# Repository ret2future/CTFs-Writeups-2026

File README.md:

# CTFs 2026 Organized

This folder groups 2026 CTF challenges by event.

- Structure uses symlinks to original challenge folders (no duplicate copies).
- Each challenge appears under one CTF event in this organized view.
- Source folders remain unchanged.

Events included:

- UMassCTF_2026
- Index_2026_TAMUctf
- DawgCTF_2026
- Midnight_Flag_CTF_EXECUTION_2026
- PsychCTF_2026
- UTCTF_2026
- BlueHens_CTF_2026
- RedFox_CTF_2026
- Ramadan_CTF_2026
- Incognito_7_0_2026
- Squ1rrel_CTF_2026

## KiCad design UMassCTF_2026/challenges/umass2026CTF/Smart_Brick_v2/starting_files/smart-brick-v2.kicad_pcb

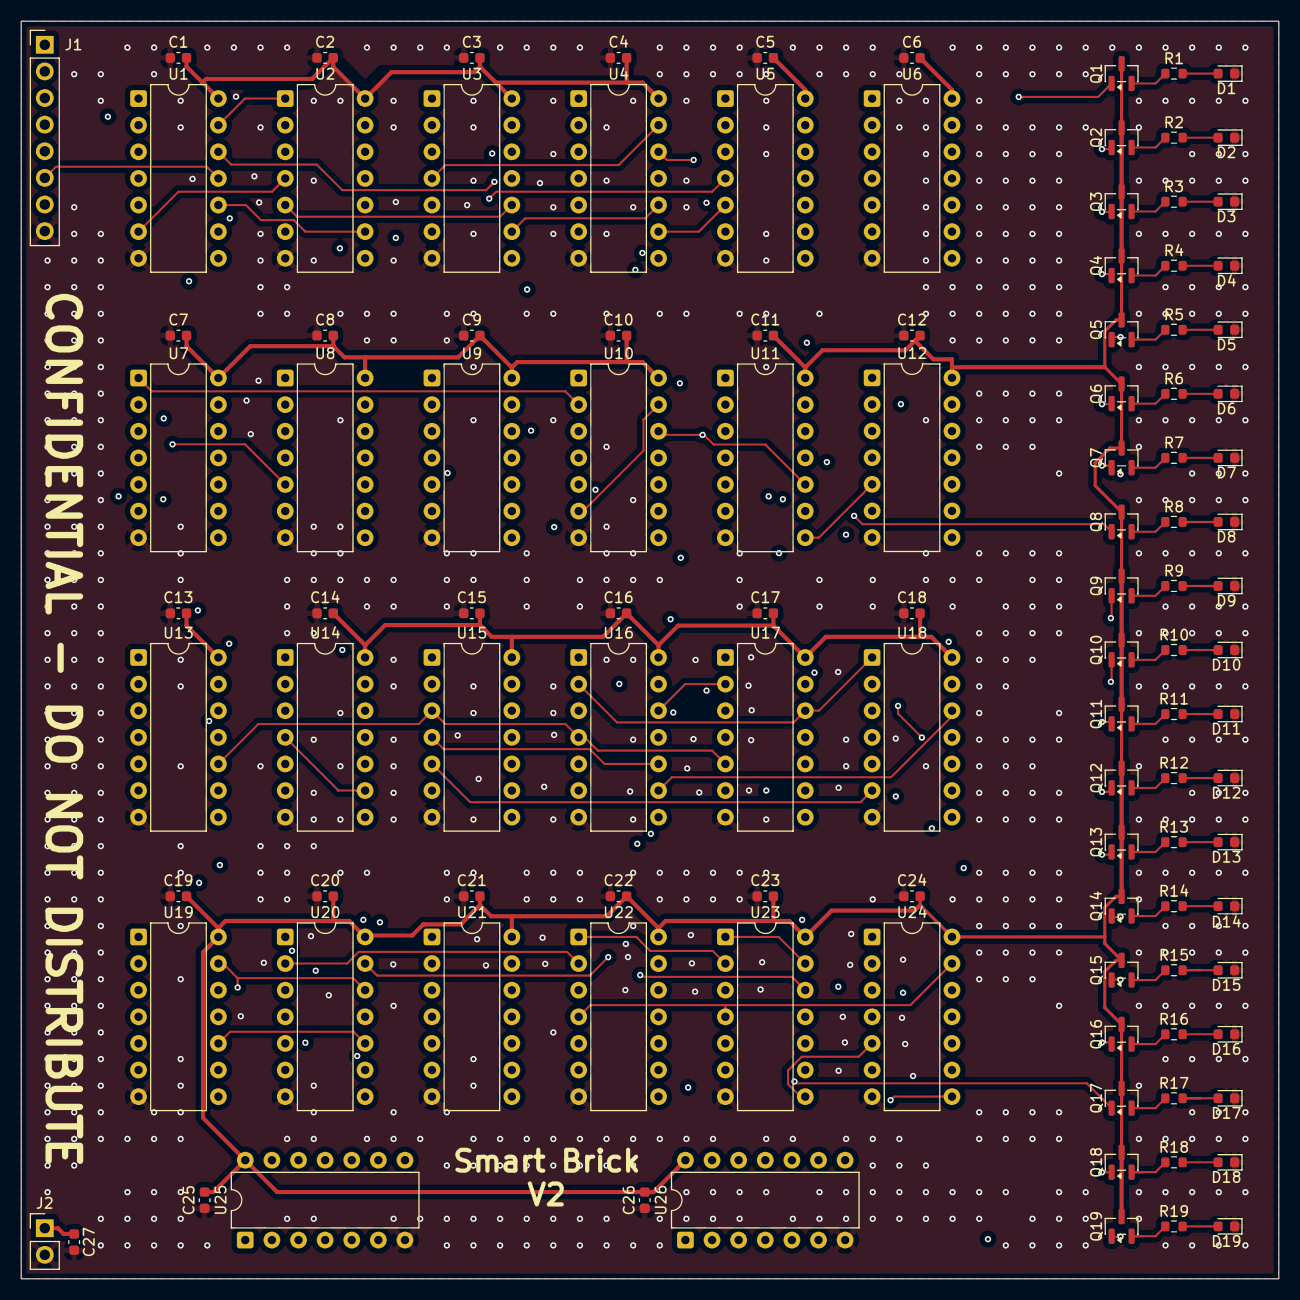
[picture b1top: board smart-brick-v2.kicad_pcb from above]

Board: 4 copper layers, 120.0 x 120.0 mm, 112 parts (0 on the bottom side), 109 nets.

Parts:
C1, C2, C3, C4, C5, C6, C7, C8, C9, C10, C11, C12, C13, C14, C15, C16, C17, C18, C19, C20, C21, C22, C23, C24, C25, C26: .1u; C_0603_1608Metric
C27: 10u; C_0603_1608Metric
D1, D2, D3, D4, D5, D6, D7, D8, D9, D10, D11, D12, D13, D14, D15, D16, D17, D18, D19: LED; LED_0603_1608Metric
J1: Conn_01x08; PinHeader_1x08_P2.54mm_Vertical
J2: Conn_01x02; PinHeader_1x02_P2.54mm_Vertical
Q1, Q2, Q3, Q4, Q5, Q6, Q7, Q8, Q9, Q10, Q11, Q12, Q13, Q14, Q15, Q16, Q17, Q18, Q19: 2N7002; SOT-23
R1, R2, R3, R4, R5, R6, R7, R8, R9, R10, R11, R12, R13, R14, R15, R16, R17, R18, R19: 1K; R_0603_1608Metric
U1, U6: 74LS04; DIP-14_W7.62mm
U2, U4, U7, U10, U11, U12, U13, U16, U19, U20, U21, U22, U23, U24, U25: 74LS21; DIP-14_W7.62mm
U3, U15: 74LS27; DIP-14_W7.62mm
U5: 74LS08; DIP-14_W7.62mm
U8: 74LS32; DIP-14_W7.62mm
U9: 74LS86; DIP-14_W7.62mm
U14: 74LS00; DIP-14_W7.62mm
U17, U26: 74LS02; DIP-14_W7.62mm
U18: 74LS20; DIP-14_W7.62mm

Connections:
+5V: C1.1, C2.1, C3.1, C4.1, C5.1, C6.1, C7.1, C8.1, C9.1, C10.1, C11.1, C12.1, C13.1, C14.1, C15.1, C16.1, C17.1, C18.1, C19.1, C20.1, C21.1, C22.1, C23.1, C24.1, C25.1, C26.1, C27.1, J2.1, Q1.3 (D), Q2.3 (D), Q3.3 (D), Q4.3 (D), Q5.3 (D), Q6.3 (D), Q7.3 (D), Q8.3 (D), Q9.3 (D), Q10.3 (D), Q11.3 (D), Q12.3 (D), Q13.3 (D), Q14.3 (D), Q15.3 (D), Q16.3 (D), Q17.3 (D), Q18.3 (D), Q19.3 (D), U1.14 (VCC), U2.14 (VCC), U3.14 (VCC), U4.14 (VCC), U5.14 (VCC), U6.14 (VCC), U7.14 (VCC), U8.14 (VCC), U9.14 (VCC), U10.14 (VCC), U11.14 (VCC), U12.14 (VCC), U13.14 (VCC), U14.14 (VCC), U15.14 (VCC), U16.14 (VCC), U17.14 (VCC), U18.14 (VCC), U19.14 (VCC), U20.14 (VCC), U21.14 (VCC), U22.14 (VCC), U23.14 (VCC), U24.14 (VCC), U25.14 (VCC), U26.14 (VCC)
/G0: U1.2, U8.5, U14.1, U14.10, U22.1, U23.2
/G1: U1.4, U2.5, U3.10, U7.4, U8.9, U12.4, U16.2, U17.12, U18.1, U22.4, U23.4, U24.13
/G2: U1.6, U2.4, U5.9, U7.1, U10.2, U16.1, U16.12, U17.2, U20.13, U21.9, U22.9, U24.1
/G3: U1.8, U3.4, U4.13, U11.12, U15.2, U18.2, U20.9
/G4: U1.10, U2.9, U3.3, U4.9, U5.5, U10.12, U11.10, U13.10, U15.3, U16.4, U17.5, U20.4, U21.2
/G5: U1.12, U15.13, U16.9, U18.12, U21.13
/G6: U2.6, U2.13
/G7: U2.8, U14.4, U14.9
/G8: U3.12, U4.5
/G9: U4.6, U5.2
/G10: U5.3, U17.8, U17.11
/G11: U6.2, U7.2, U8.1, U9.1, U10.5, U12.2, U18.9, U19.2, U24.2
/G12: U4.8, U7.5
/G13: Q3.1 (G), U7.6
/G14: U8.3, U9.4
/G15: U9.3, U9.5
/G16: U5.4, U9.6
/G17: U5.6, U7.13
/G18: U5.10, U7.8
/G19: Q4.1 (G), U5.8
/G20: U10.6, U10.13
/G21: Q5.1 (G), U10.8
/G22: U3.5, U8.6
/G23: U3.6, U11.5
/G24: Q6.1 (G), U11.6
/G25: U11.8, U12.5
/G26: Q7.1 (G), U12.6
/G27: U3.8, U12.13
/G28: U5.13, U12.8
/G29: Q8.1 (G), U5.11
/G30: U13.6, U13.13
/G31: Q9.1 (G), U13.8
/G34: U14.3, U15.1
/G35: U15.12, U16.5
/G36: Q10.1 (G), U16.6
/G37: U17.1, U18.5
/G38: U15.5, U18.6
/G39: Q11.1 (G), U15.6
/G40: U16.8, U19.5
/G41: Q12.1 (G), U19.6
/G42: U19.8, U20.5
/G43: Q13.1 (G), U20.6
/G44: U20.8, U21.5
/G45: Q14.1 (G), U21.6
/G46: U21.8, U22.5
/G47: Q15.1 (G), U22.6
/G48: U22.8, U23.5
/G49: Q16.1 (G), U23.6
/G50: U8.13, U18.8
/G51: U8.11, U17.6
/G52: Q17.1 (G), U17.4
/G53: U23.8, U24.5
/G54: Q18.1 (G), U24.6
/G55: U24.8, U25.5
/G56: Q19.1 (G), U25.6
/G57: U14.6, U14.12
/G58: U14.8, U14.13
/G59: Q1.1 (G), U14.11
/G60: U17.10, U26.2
/G61: U17.13, U26.3
/G62: Q2.1 (G), U26.1
/IN0: J1.1, U1.1, U2.2, U3.9, U4.1, U4.10, U8.2, U9.2, U10.1, U11.13, U13.5, U14.5, U15.4, U16.10, U18.10, U19.9, U21.4, U24.4, U25.1
/IN1: J1.2, U1.3, U3.1, U7.12, U10.9, U11.1, U13.9, U16.13, U17.9, U19.10, U20.10, U23.10
/IN2: J1.3, U2.12, U4.2, U5.12, U6.1, U8.4, U13.12, U14.2, U17.3, U20.1, U21.1, U21.10, U22.13, U24.10
/IN3: J1.4, U1.5, U4.4, U8.10, U11.2, U11.9, U12.12, U13.2, U19.12, U24.12
/IN4: J1.5, U1.9, U2.10, U3.2, U3.11, U7.9, U10.4, U13.4, U18.13, U19.4, U20.2, U22.2, U22.10, U23.12, U25.2
/IN5: J1.6, U1.11, U3.13, U12.10, U19.1, U21.12, U22.12, U23.9, U25.4
/IN6: J1.7, U1.13, U2.1, U4.12, U5.1, U7.10, U10.10, U11.4, U12.1, U12.9, U13.1, U18.4, U19.13, U20.12, U23.1, U23.13, U24.9
/INT1: U8.8, U8.12
GND: C1.2, C2.2, C3.2, C4.2, C5.2, C6.2, C7.2, C8.2, C9.2, C10.2, C11.2, C12.2, C13.2, C14.2, C15.2, C16.2, C17.2, C18.2, C19.2, C20.2, C21.2, C22.2, C23.2, C24.2, C25.2, C26.2, C27.2, D1.1 (K), D2.1 (K), D3.1 (K), D4.1 (K), D5.1 (K), D6.1 (K), D7.1 (K), D8.1 (K), D9.1 (K), D10.1 (K), D11.1 (K), D12.1 (K), D13.1 (K), D14.1 (K), D15.1 (K), D16.1 (K), D17.1 (K), D18.1 (K), D19.1 (K), J1.8, J2.2, U1.7 (GND), U2.7 (GND), U3.7 (GND), U4.7 (GND), U5.7 (GND), U6.7 (GND), U7.7 (GND), U8.7 (GND), U9.7 (GND), U10.7 (GND), U11.7 (GND), U12.7 (GND), U13.7 (GND), U14.7 (GND), U15.7 (GND), U16.7 (GND), U17.7 (GND), U18.7 (GND), U19.7 (GND), U20.7 (GND), U21.7 (GND), U22.7 (GND), U23.7 (GND), U24.7 (GND), U25.7 (GND), U26.7 (GND)
unnamed: D1.2 (A), R1.2
unnamed: D2.2 (A), R2.2
unnamed: D3.2 (A), R3.2
unnamed: D4.2 (A), R4.2
unnamed: D5.2 (A), R5.2
unnamed: D6.2 (A), R6.2
unnamed: D7.2 (A), R7.2
unnamed: D8.2 (A), R8.2
unnamed: D9.2 (A), R9.2
unnamed: D10.2 (A), R10.2
unnamed: D11.2 (A), R11.2
unnamed: D12.2 (A), R12.2
unnamed: D13.2 (A), R13.2
unnamed: D14.2 (A), R14.2
unnamed: D15.2 (A), R15.2
unnamed: D16.2 (A), R16.2
unnamed: D17.2 (A), R17.2
unnamed: D18.2 (A), R18.2
unnamed: D19.2 (A), R19.2
unnamed: Q1.2 (S), R1.1
unnamed: Q2.2 (S), R2.1
unnamed: Q3.2 (S), R3.1
unnamed: Q4.2 (S), R4.1
unnamed: Q5.2 (S), R5.1
unnamed: Q6.2 (S), R6.1
unnamed: Q7.2 (S), R7.1
unnamed: Q8.2 (S), R8.1
unnamed: Q9.2 (S), R9.1
unnamed: Q10.2 (S), R10.1
unnamed: Q11.2 (S), R11.1
unnamed: Q12.2 (S), R12.1
unnamed: Q13.2 (S), R13.1
unnamed: Q14.2 (S), R14.1
unnamed: Q15.2 (S), R15.1
unnamed: Q16.2 (S), R16.1
unnamed: Q17.2 (S), R17.1
unnamed: Q18.2 (S), R18.1
unnamed: Q19.2 (S), R19.1

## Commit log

2026-04-20 added current ctf files regardless of having write-up or not. some may contain the exploit, some not
2026-04-20 Replace local symlinks with actual challenge content
2026-04-20 Add Psych, Ramadan, RedFox, Squ1rrel, and UMass writeup folders (excluding oversized files)
2026-04-20 Add visible DawgCTF challenge directories for GitHub browsing
